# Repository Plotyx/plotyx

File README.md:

## Plotyx - Open-source XY plotter
Plotyx is an open-source XY pen plotter, built using a mix of 3D printed and off-the-shelf parts. It focus on using linear rails for precise movement and accuracy, and provides a working area of just over A3 paper size.  
<br>

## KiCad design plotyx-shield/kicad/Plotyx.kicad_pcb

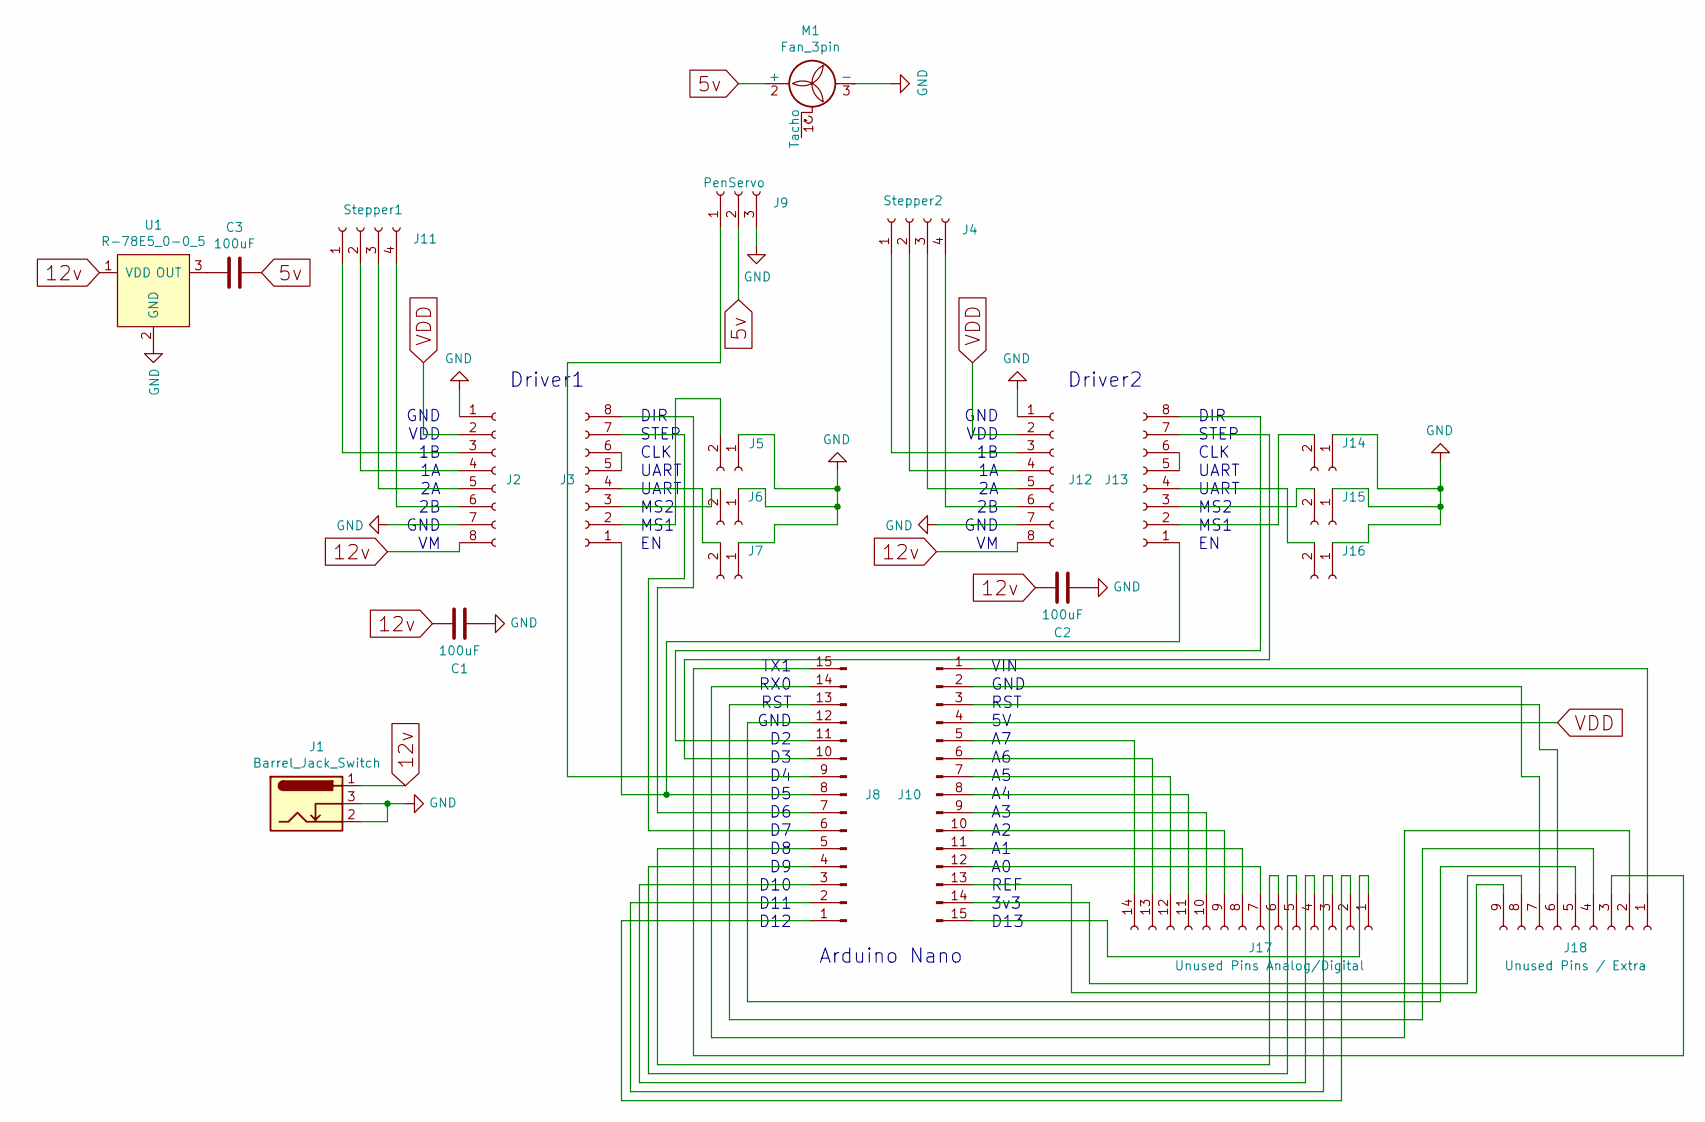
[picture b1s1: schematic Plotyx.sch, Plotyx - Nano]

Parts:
C1, C2, C3: 100uF; C_Radial_D5.0mm_H11.0mm_P2.00mm
J1: Barrel_Jack_Switch; BarrelJack_Horizontal
J2, J3, J12, J13: Conn_01x08_Female; PinSocket_1x08_P2.54mm_Vertical
J4: Stepper2; PinHeader_1x04_P2.54mm_Vertical
J5, J6, J7, J14, J15, J16: Conn_01x02_Female; PinHeader_1x02_P2.54mm_Vertical
J8, J10: Conn_01x15_Male; PinSocket_1x15_P2.54mm_Vertical
J9: PenServo; PinHeader_1x03_P2.54mm_Vertical
J11: Stepper1; PinHeader_1x04_P2.54mm_Vertical
J17: Unused Pins Analog/Digital; PinSocket_1x14_P2.54mm_Vertical
J18: Unused Pins / Extra; PinSocket_1x09_P2.54mm_Vertical
M1: Fan_3pin; FanPinHeader_1x03_P2.54mm_Vertical
U1: R-78E5_0-0_5; SIP-3_P2.54mm; MPN R-78E5.0-0.5; Digi-Key_PN 945-1648-5-ND

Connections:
5v: C3.1, J9.2, M1.2 (+)
12v: C1.2, C2.2, J1.1, J2.8, J12.8, U1.1 (VDD)
GND: C1.1, C2.1, J1.2, J1.3, J2.1, J2.7, J5.1, J6.1, J7.1, J9.3, J12.1, J12.7, J14.1, J15.1, J16.1, M1.3 (-), U1.2 (GND)
unnamed: C3.2, U1.3 (OUT)
unnamed: J3.2, J5.2
unnamed: J3.3, J6.2
unnamed: J3.4, J7.2
unnamed: J3.5, J3.6
unnamed: J3.7, J8.6
unnamed: J3.8, J8.7
unnamed: J8.9, J9.1
unnamed: J10.1, J18.1
unnamed: J10.2, J18.7
unnamed: J10.3, J18.6
unnamed: J10.5, J17.14
unnamed: J10.6, J17.13
unnamed: J10.7, J17.12
unnamed: J10.8, J17.11
unnamed: J10.9, J17.10
unnamed: J10.10, J17.9
unnamed: J10.11, J17.8
unnamed: J10.12, J17.7
unnamed: J10.13, J18.9
unnamed: J10.14, J18.8
unnamed: J10.15, J17.1
unnamed: J2.3, J11.1
unnamed: J2.4, J11.2
unnamed: J2.5, J11.3
unnamed: J2.6, J11.4
unnamed: J4.1, J12.3
unnamed: J4.2, J12.4
unnamed: J4.3, J12.5
unnamed: J4.4, J12.6
unnamed: J3.1, J8.8, J13.1
unnamed: J13.2, J14.2
unnamed: J13.3, J15.2
unnamed: J13.4, J16.2
unnamed: J13.5, J13.6
unnamed: J8.10, J13.7
unnamed: J8.11, J13.8
unnamed: J8.1, J17.2
unnamed: J8.2, J17.3
unnamed: J8.3, J17.4
unnamed: J8.4, J17.5
unnamed: J8.5, J17.6
unnamed: J8.14, J18.2
unnamed: J8.15, J18.3
unnamed: J8.13, J18.4
unnamed: J8.12, J18.5
VDD: J2.2, J10.4, J12.2

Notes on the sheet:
GND VDD 1B 1A 2A 2B GND VM
DIR STEP CLK UART UART MS2 MS1 EN
Driver2
Driver1
Arduino Nano
VIN GND RST 5V A7 A6 A5 A4 A3 A2 A1 A0 REF 3v3 D13
TX1 RX0 RST GND D2 D3 D4 D5 D6 D7 D8 D9 D10 D11 D12

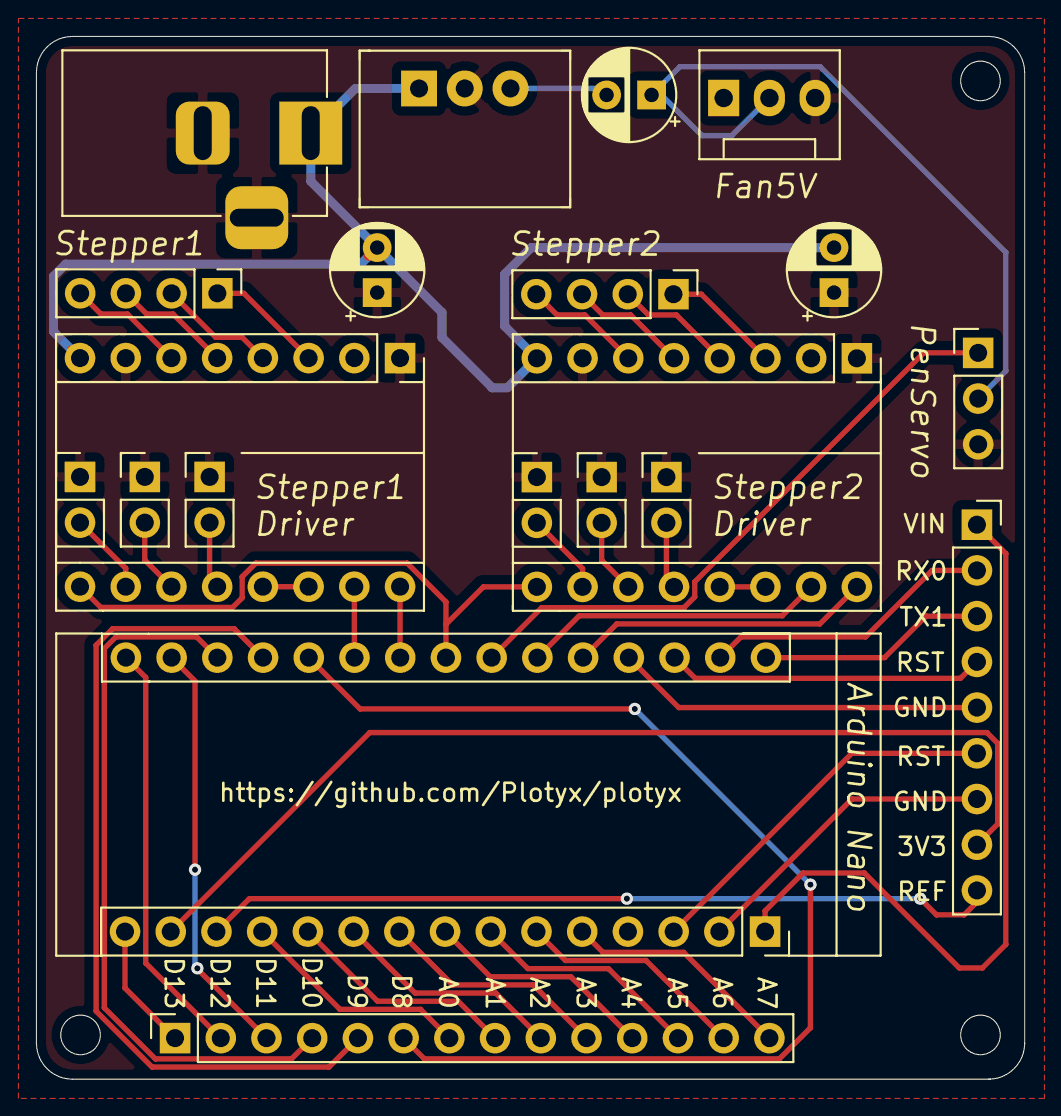
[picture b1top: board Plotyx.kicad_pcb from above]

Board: 2 copper layers, 54.9 x 57.9 mm, 23 parts (0 on the bottom side), 50 nets.

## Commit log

2020-04-14 README.md
2020-05-28 Added Arduino Plotyx Shield project files
2020-06-22 Removing Support for Plotyx-Shield

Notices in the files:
plotyx-shield/kicad/Plotyx.sch:
https://creativecommons.org/licenses/by/4.0
License: CC BY-4.0
